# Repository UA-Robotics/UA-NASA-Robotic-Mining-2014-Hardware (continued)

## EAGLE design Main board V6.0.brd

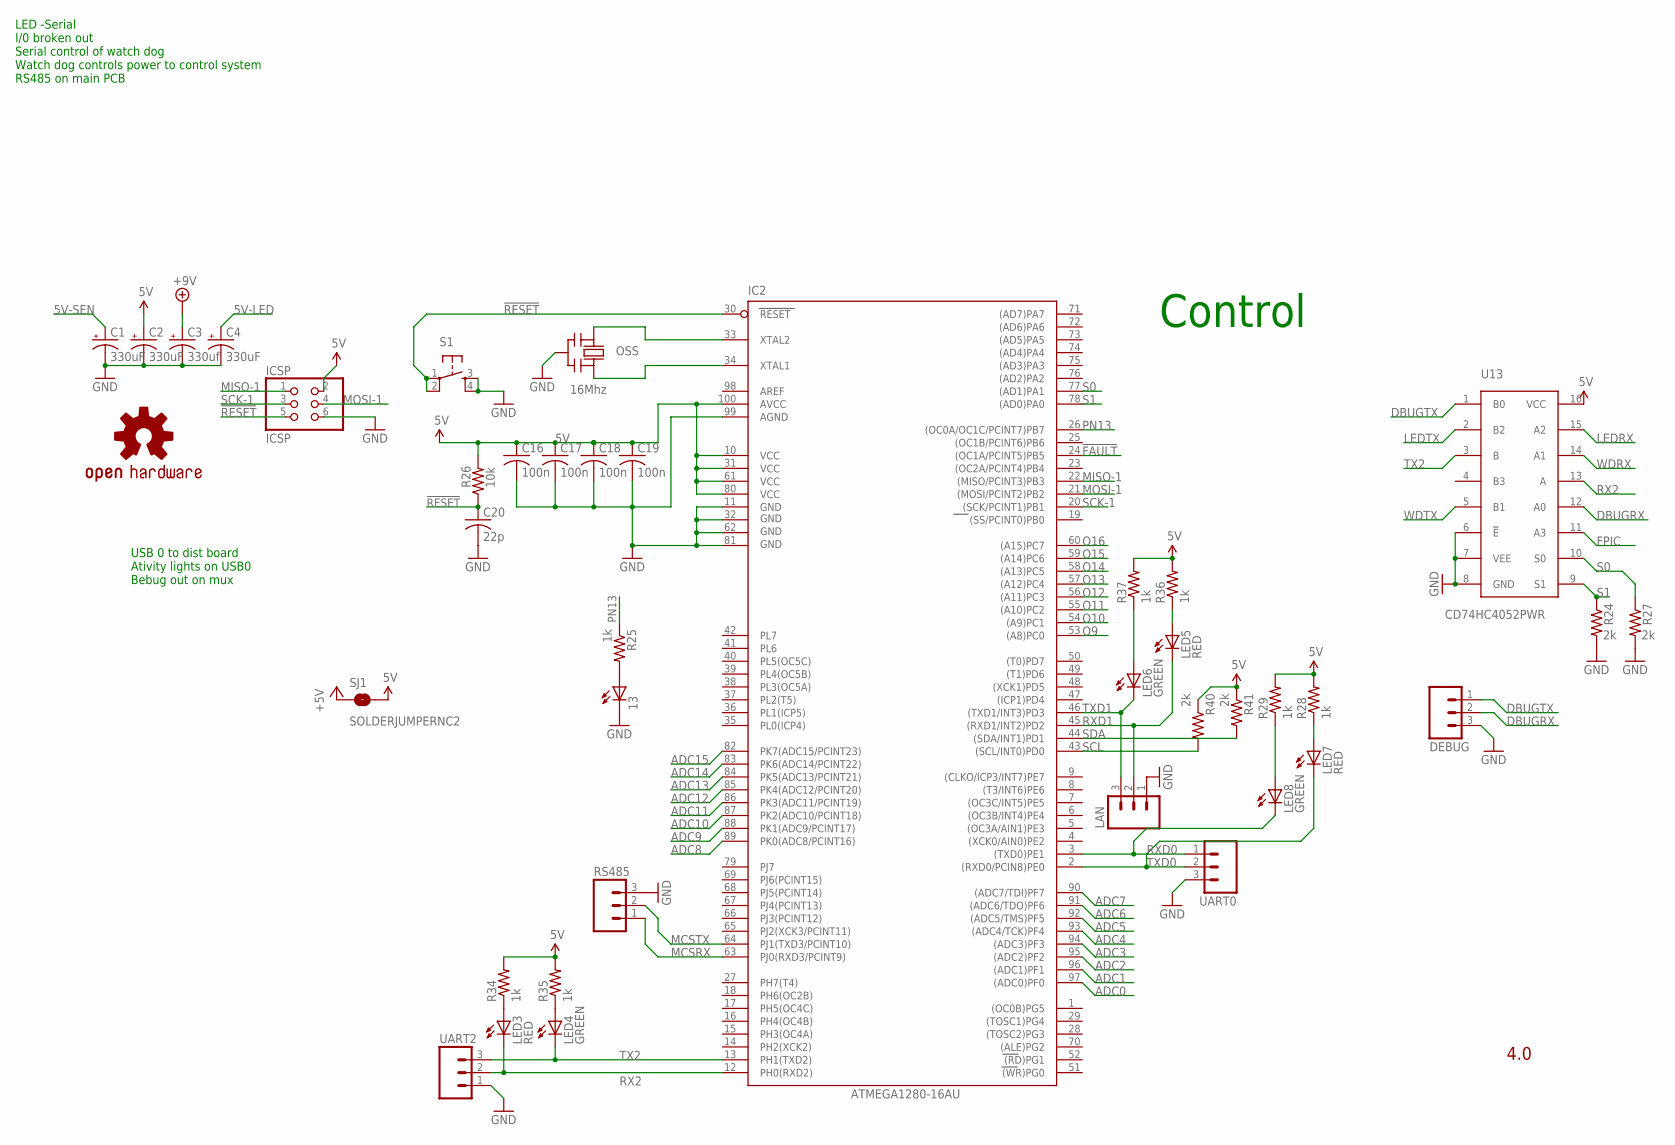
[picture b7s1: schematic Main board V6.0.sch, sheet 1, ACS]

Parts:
13: LEDCHIP-LED0805; CHIP-LED0805
C1, C2, C4: 330uF; 140CLH-0810
C3: 330uf; 140CLH-0810
C16, C17, C18, C19: 100n; C0805
C20: 22p; C0805
DEBUG: M03LOCK; 1X03_LOCK
IC2: ATMEGA1280-16AU; TQFP100
ICSP: ICSP; 2X03
LAN: M03LOCK; 1X03_LOCK
LED3, LED5, LED7: RED; CHIP-LED0805
LED4, LED6, LED8: GREEN; CHIP-LED0805
OSS: 16Mhz; AWCSR
R24, R27, R40, R41: 2k; R0805
R25, R28, R29, R34, R35, R36, R37: 1k; R0805
R26: 10k; R0805
RS485: M03LOCK; 1X03_LOCK
S1: TAC_SWITCHSMD; TACTILE_SWITCH_SMD
SJ1: SOLDERJUMPERNC2; SJ_2S-NOTRACE
U13: CD74HC4052PWR; TSSOP-16
U$3: OSHW-LOGOL; OSHW-LOGO-L
UART0: M03LOCK; 1X03_LOCK
UART2: M03POLAR; MOLEX-1X3

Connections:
5V: C2.+, C16.1, C17.1, C18.1, C19.1, IC2.10 (VCC), IC2.31 (VCC1), IC2.61 (VCC2), IC2.80 (VCC3), IC2.100 (AVCC), ICSP.2, R26.2, R28.2, R29.2, R34.2, R35.2, R36.2, R37.2, R40.1, R41.1, SJ1.2, U13.16 (VCC); also elsewhere on the board
5V-LED: C4.+; also elsewhere on the board
5V-SEN: C1.+; also elsewhere on the board
!FAULT: IC2.24 ((OC1A/PCINT5)PB5)
!RESET: C20.1, IC2.30 (RESET), ICSP.5, R26.1, S1.1, S1.2
+5V: SJ1.1; also elsewhere on the board
+9V: C3.+; also elsewhere on the board
ADC0: IC2.97 ((ADC0)PF0); also elsewhere on the board
ADC1: IC2.96 ((ADC1)PF1); also elsewhere on the board
ADC2: IC2.95 ((ADC2)PF2); also elsewhere on the board
ADC3: IC2.94 ((ADC3)PF3); also elsewhere on the board
ADC4: IC2.93 ((ADC4/TCK)PF4); also elsewhere on the board
ADC5: IC2.92 ((ADC5/TMS)PF5); also elsewhere on the board
ADC6: IC2.91 ((ADC6/TDO)PF6); also elsewhere on the board
ADC7: IC2.90 ((ADC7/TDI)PF7); also elsewhere on the board
ADC8: IC2.89 (PK0(ADC8/PCINT16)); also elsewhere on the board
ADC9: IC2.88 (PK1(ADC9/PCINT17)); also elsewhere on the board
ADC10: IC2.87 (PK2(ADC10/PCINT18)); also elsewhere on the board
ADC11: IC2.86 (PK3(ADC11/PCINT19)); also elsewhere on the board
ADC12: IC2.85 (PK4(ADC12/PCINT20)); also elsewhere on the board
ADC13: IC2.84 (PK5(ADC13/PCINT21)); also elsewhere on the board
ADC14: IC2.83 (PK6(ADC14/PCINT22)); also elsewhere on the board
ADC15: IC2.82 (PK7(ADC15/PCINT23)); also elsewhere on the board
DBUGRX: DEBUG.2, U13.12 (A0)
DBUGTX: DEBUG.1, U13.1 (B0)
FPIC: U13.11 (A3); also elsewhere on the board
GND: 13.C, C1.-, C2.-, C3.-, C4.-, C16.2, C17.2, C18.2, C19.2, C20.2, DEBUG.3, IC2.11 (GND), IC2.32 (GND1), IC2.62 (GND2), IC2.81 (GND3), IC2.99 (AGND), ICSP.6, LAN.1, OSS.2 (GND), R24.2, R27.2, RS485.3, S1.3, S1.4, U13.6 (!E), U13.7 (VEE), U13.8 (GND), UART0.3, UART2.1; also elsewhere on the board
LEDRX: U13.15 (A2); also elsewhere on the board
LEDTX: U13.2 (B2); also elsewhere on the board
MCSRX: IC2.63 (PJ0(RXD3/PCINT9)), RS485.1; also elsewhere on the board
MCSTX: IC2.64 (PJ1(TXD3/PCINT10)), RS485.2; also elsewhere on the board
MISO-1: IC2.22 ((MISO/PCINT3)PB3), ICSP.1
MOSI-1: IC2.21 ((MOSI/PCINT2)PB2), ICSP.4
unnamed: 13.A, R25.2
unnamed: IC2.34 (XTAL1), OSS.3 (OUT)
unnamed: IC2.33 (XTAL2), OSS.1 (IN)
unnamed: LED8.A, R29.1
unnamed: LED4.A, R35.1
unnamed: LED3.A, R34.1
unnamed: LED7.A, R28.1
unnamed: LED6.A, R37.1
unnamed: LED5.A, R36.1
O9: IC2.53 ((A8)PC0)
O10: IC2.54 ((A9)PC1)
O11: IC2.55 ((A10)PC2)
O12: IC2.56 ((A11)PC3)
O13: IC2.57 ((A12)PC4)
O14: IC2.58 ((A13)PC5)
O15: IC2.59 ((A14)PC6)
O16: IC2.60 ((A15)PC7)
PN13: IC2.26 ((OC0A/OC1C/PCINT7)PB7), R25.1; also elsewhere on the board
RX2: IC2.12 (PH0(RXD2)), LED3.C, U13.13 (A), UART2.2
RXD0: IC2.3 ((TXD0)PE1), LED8.C, UART0.1; also elsewhere on the board
RXD1: IC2.45 ((RXD1/INT2)PD2), LAN.2, LED5.C; also elsewhere on the board
S0: IC2.77 ((AD1)PA1), R27.1, U13.10 (S0)
S1: IC2.78 ((AD0)PA0), R24.1, U13.9 (S1)
SCK-1: IC2.20 ((SCK/PCINT1)PB1), ICSP.3
SCL: IC2.43 ((SCL/INT0)PD0), R40.2; also elsewhere on the board
SDA: IC2.44 ((SDA/INT1)PD1), R41.2; also elsewhere on the board
TX2: IC2.13 (PH1(TXD2)), LED4.C, U13.3 (B), UART2.3
TXD0: IC2.2 ((RXD0/PCIN8)PE0), LED7.C, UART0.2; also elsewhere on the board
TXD1: IC2.46 ((TXD1/INT3)PD3), LAN.3, LED6.C; also elsewhere on the board
WDRX: U13.14 (A1); also elsewhere on the board
WDTX: U13.5 (B1); also elsewhere on the board

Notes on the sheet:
4.0
Control
LED -Serial I/0 broken out Serial control of watch dog Watch dog controls power to control system RS485 on main PCB
USB 0 to dist board Ativity lights on USB0 Bebug out on mux

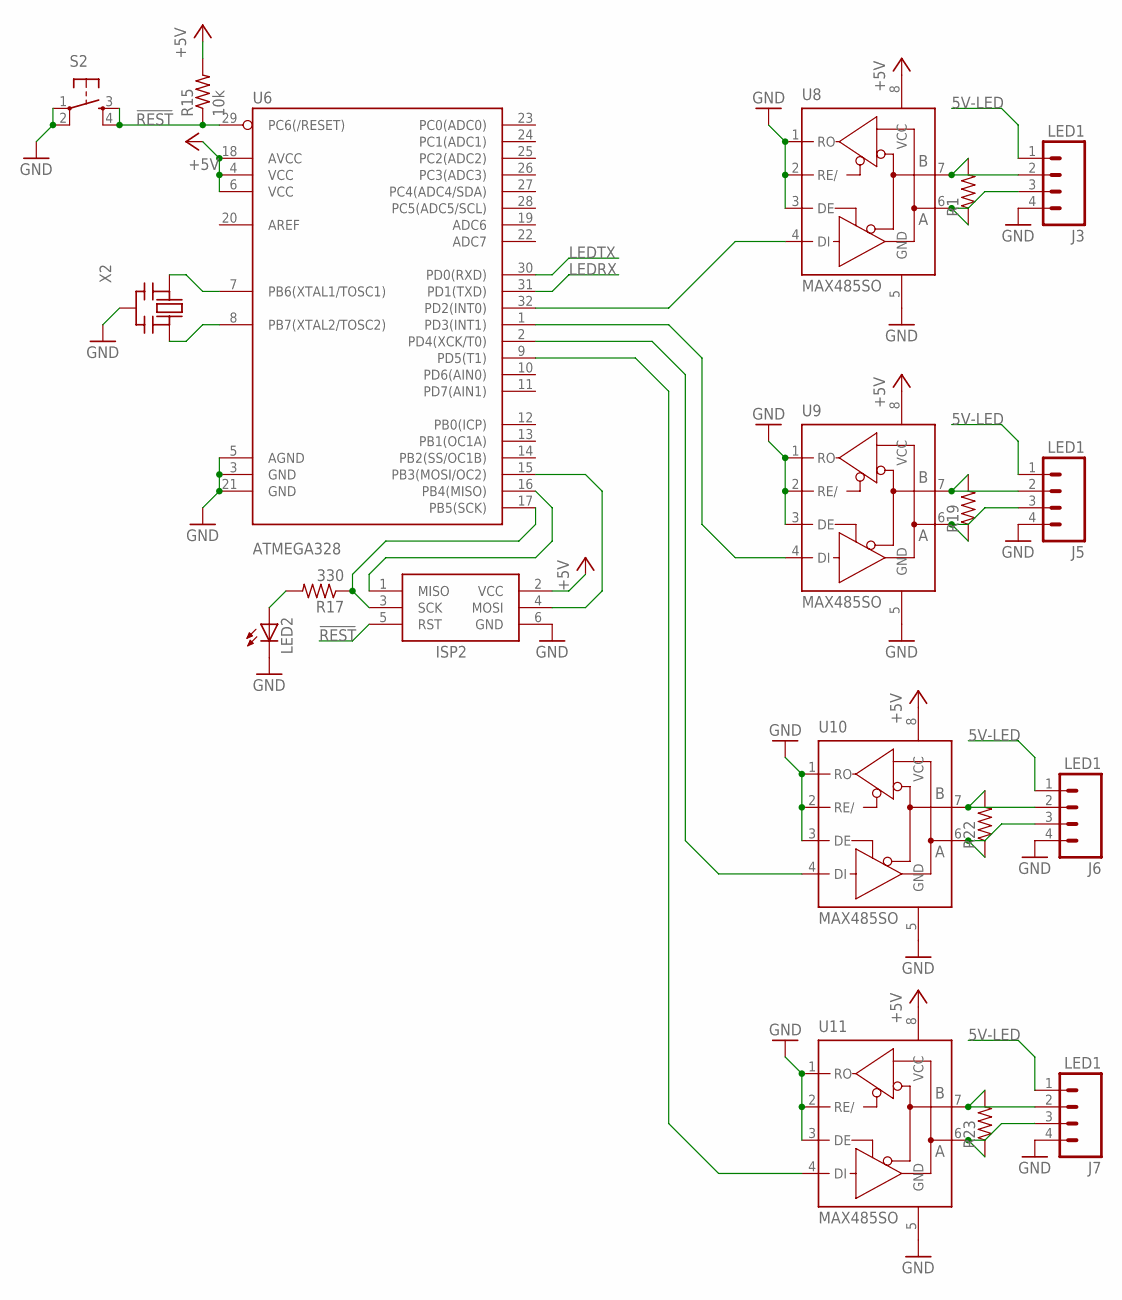
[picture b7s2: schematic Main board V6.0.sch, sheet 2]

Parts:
ISP2: AVRISP-6; AVRISP
J3, J5, J6, J7: LED1; M4
LED2: LEDCHIPLED_0805; CHIPLED_0805
R1, R19, R22, R23: RESISTOR0805-RES; 0805
R15: 10k; R0805
R17: 330; R0805
S2: TAC_SWITCHPTH; TACTILE-PTH
U6: ATMEGA328; TQFP32-08
U8, U9, U10, U11: MAX485SO; SO08
X2: CERMOSCILL-AWCSR; AWCSR

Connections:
5V-LED: J3.1, J5.1, J6.1, J7.1; also elsewhere on the board
!REST: ISP2.5 (RST), R15.1, S2.3, S2.4, U6.29 (PC6(/RESET))
+5V: ISP2.2 (VCC), R15.2, U6.4 (VCC), U6.6 (VCC), U6.18 (AVCC), U8.8 (VCC), U9.8 (VCC), U10.8 (VCC), U11.8 (VCC); also elsewhere on the board
DFDFD: ISP2.1 (MISO), U6.16 (PB4(MISO))
GND: ISP2.6 (GND), J3.4, J5.4, J6.4, J7.4, LED2.C, S2.1, S2.2, U6.3 (GND), U6.5 (AGND), U6.21 (GND), U8.1 (RO), U8.2 (RE/), U8.3 (DE), U8.5 (GND), U9.1 (RO), U9.2 (RE/), U9.3 (DE), U9.5 (GND), U10.1 (RO), U10.2 (RE/), U10.3 (DE), U10.5 (GND), U11.1 (RO), U11.2 (RE/), U11.3 (DE), U11.5 (GND), X2.2 (GND); also elsewhere on the board
LEDRX: U6.31 (PD1(TXD)); also elsewhere on the board
LEDTX: U6.30 (PD0(RXD)); also elsewhere on the board
unnamed: ISP2.3 (SCK), R17.1, U6.17 (PB5(SCK))
unnamed: ISP2.4 (MOSI), U6.15 (PB3(MOSI/OC2))
unnamed: LED2.A, R17.2
unnamed: U6.7 (PB6(XTAL1/TOSC1)), X2.1 (IN)
unnamed: U6.8 (PB7(XTAL2/TOSC2)), X2.3 (OUT)
unnamed: J3.2, R1.2, U8.7 (B)
unnamed: J3.3, R1.1, U8.6 (A)
unnamed: J5.2, R19.2, U9.7 (B)
unnamed: J5.3, R19.1, U9.6 (A)
unnamed: J6.2, R22.2, U10.7 (B)
unnamed: J6.3, R22.1, U10.6 (A)
unnamed: J7.2, R23.2, U11.7 (B)
unnamed: J7.3, R23.1, U11.6 (A)
unnamed: U6.32 (PD2(INT0)), U8.4 (DI)
unnamed: U6.1 (PD3(INT1)), U9.4 (DI)
unnamed: U6.2 (PD4(XCK/T0)), U10.4 (DI)
unnamed: U6.9 (PD5(T1)), U11.4 (DI)

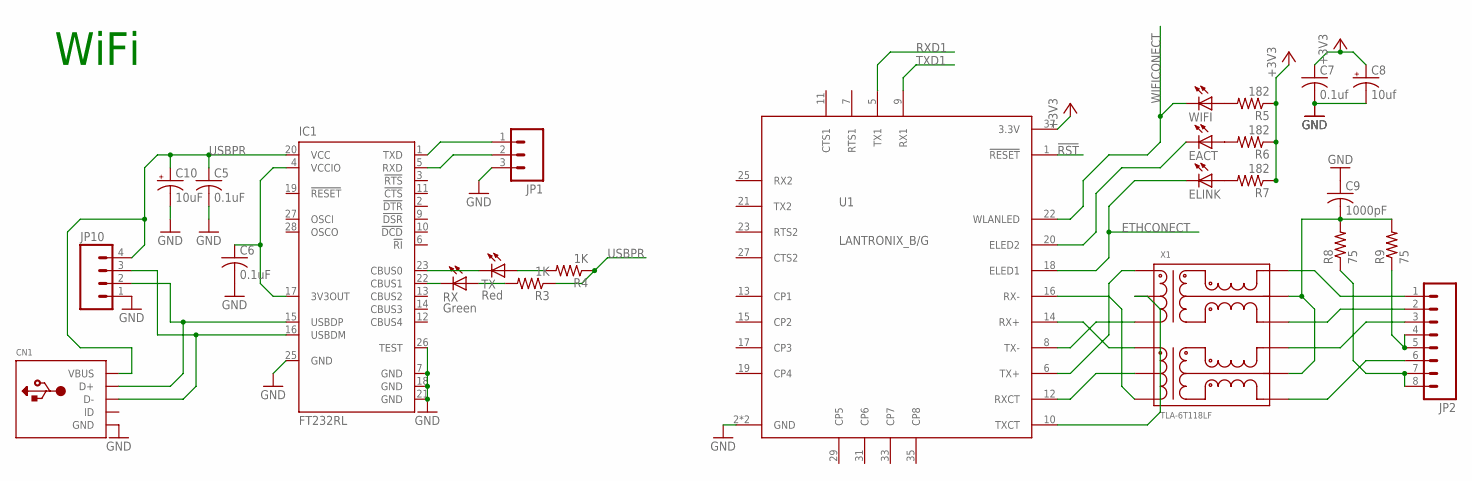
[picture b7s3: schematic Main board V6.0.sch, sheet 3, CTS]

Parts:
C5, C6: 0.1uF; C0805K
C7: 0.1uf; C0805K
C8: 10uf; EIA3528
C9: 1000pF; C1812
C10: 10uF; EIA3528-KIT
CN1: USBMINIB; USB-MINIB
EACT: LEDCHIP-LED0805; CHIP-LED0805
ELINK: LEDCHIP-LED0805; CHIP-LED0805
IC1: FT232RL; SSOP28
JP1: M03POLAR; MOLEX-1X3
JP2: M08LOCK; 1X08_LOCK
JP10: M04POLAR; MOLEX-1X4
R3, R4: 1K; R0805
R5, R6, R7: 182; R0805
R8, R9: 75; R0805
RX: Green; CHIP-LED0805
TX: Red; CHIP-LED0805
U1: LANTRONIX_B/G; LANA/BTH
WIFI: LEDCHIP-LED0805; CHIP-LED0805
X1: TLA-6T118LF; SO-16MOD

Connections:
!RST: U1.1 (!RESET)
+3V3: C7.1, C8.A (+), R5.1, R6.1, R7.1, U1.37 (3.3V); also elsewhere on the board
ETHCONECT: ELINK.C, U1.18 (ELED1)
GND: C5.2, C6.2, C7.2, C8.C (-), C9.1, C10.C (-), CN1.GND, IC1.7 (GND), IC1.18 (GND), IC1.21 (GND), IC1.25 (GND), IC1.26 (TEST), JP1.3, JP10.1, U1.2 (GND), U1.39 (GND); also elsewhere on the board
unnamed: IC1.23 (CBUS0), TX.C
unnamed: IC1.22 (CBUS1), RX.C
unnamed: R3.2, RX.A
unnamed: CN1.D+, IC1.15 (USBDP), JP10.2
unnamed: CN1.D-, IC1.16 (USBDM), JP10.3
unnamed: R4.2, TX.A
unnamed: IC1.1 (TXD), JP1.1
unnamed: C6.1, IC1.4 (VCCIO), IC1.17 (3V3OUT)
unnamed: U1.8 (TX-), X1.3
unnamed: U1.6 (TX+), X1.1
unnamed: U1.14 (RX+), X1.6
unnamed: U1.16 (RX-), X1.8
unnamed: U1.12 (RXCT), X1.7
unnamed: U1.10 (TXCT), X1.2
unnamed: JP2.7, JP2.8, R8.1
unnamed: JP2.1, X1.16
unnamed: JP2.2, X1.14
unnamed: JP2.3, X1.11
unnamed: JP2.6, X1.9
unnamed: C9.2, R8.2, R9.2, X1.10, X1.15
unnamed: ELINK.A, R7.2
unnamed: EACT.A, R6.2
unnamed: R5.2, WIFI.A
unnamed: EACT.C, U1.20 (ELED2)
unnamed: JP2.4, JP2.5, R9.1
unnamed: IC1.5 (RXD), JP1.2
RXD1: U1.5 (TX1); also elsewhere on the board
TXD1: U1.9 (RX1); also elsewhere on the board
USBPR: C5.1, C10.A (+), CN1.VBUS, IC1.20 (VCC), JP10.4, R3.1, R4.1
WIFICONECT: U1.22 (WLANLED), WIFI.C

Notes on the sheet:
WiFi

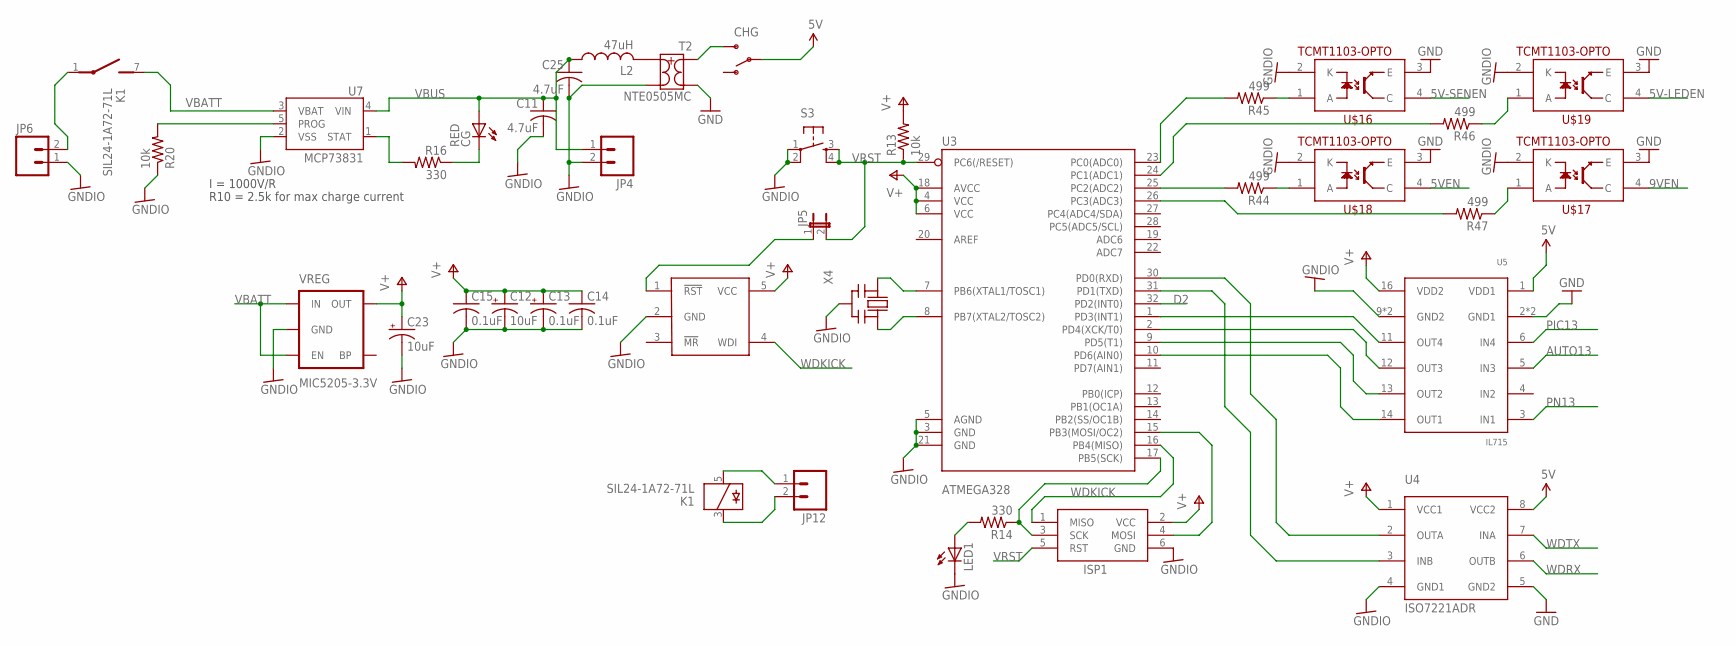
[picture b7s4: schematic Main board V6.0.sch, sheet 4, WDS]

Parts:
C11, C25: 4.7uF; C0603
C12, C23: 10uF; CT3528
C13: 0.1uF; CT3528
C14, C15: 0.1uF; C0805
CG: RED; SML0805
CHG: SWITCH-SPSTPTH; SWITCH-SPDT
ISP1: AVRISP-6; AVRISP
JP4: M021X02_NO_SILK; 1X02_NO_SILK
JP5: JUMPER-2PTH_LOCK; 1X02_LOCK
JP6: M02-JST-2MM-SMT; JST-2-SMD
JP12: M02POLAR_LOCK; MOLEX-1X2_LOCK
K1: SIL24-1A72-71L; REED
L2: 47uH; L2012C
LED1: LEDCHIPLED_0805; CHIPLED_0805
R13, R20: 10k; R0805
R14, R16: 330; R0805
R44, R45, R46, R47: 499; R0805
S3: TAC_SWITCHPTH; TACTILE-PTH
T2: NTE0505MC; SO-8FT
U3: ATMEGA328; TQFP32-08
U4: ISO7221ADR; SOIC-8
U5: IL715; S016
U7: MCP73831; SOT23-5
U20: MAX823; SOT23-5L
U$16, U$17, U$18, U$19: TCMT1103-OPTO; SSOP-4
VREG: MIC5205-3.3V; SOT23-5
X4: CERMOSCILL-CSTCRG; CSTCR-G

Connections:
5V: CHG.2, U4.8 (VCC2), U5.1 (VDD1); also elsewhere on the board
5V-LEDEN: U$19.4 (C); also elsewhere on the board
5V-SENEN: U$16.4 (C); also elsewhere on the board
5VEN: U$18.4 (C); also elsewhere on the board
9VEN: U$17.4 (C); also elsewhere on the board
AUTO13: U5.5 (IN3); also elsewhere on the board
D2: U3.32 (PD2(INT0))
GND: T2.1 (2), U4.5 (GND2), U5.2 (GND1), U5.8 (GND1), U$16.3 (E), U$17.3 (E), U$18.3 (E), U$19.3 (E); also elsewhere on the board
GNDIO: C11.2, C12.-, C13.-, C14.2, C15.2, C23.-, C25.2, ISP1.6 (GND), JP4.2, JP6.1, LED1.C, R20.1, S3.1, S3.2, T2.7 (3), U3.3 (GND), U3.5 (AGND), U3.21 (GND), U4.4 (GND1), U5.9 (GND2), U5.15 (GND2), U7.2 (VSS), U20.2 (GND), U$16.2 (K), U$17.2 (K), U$18.2 (K), U$19.2 (K), VREG.2 (GND), X4.2 (GND)
unnamed: U3.31 (PD1(TXD)), U4.3 (INB)
unnamed: JP5.1, U20.1 (!RST)
unnamed: ISP1.3 (SCK), R14.1, U3.17 (PB5(SCK))
unnamed: U3.30 (PD0(RXD)), U4.2 (OUTA)
unnamed: ISP1.4 (MOSI), U3.15 (PB3(MOSI/OC2))
unnamed: R45.2, U3.23 (PC0(ADC0))
unnamed: L2.2, T2.8 (4)
unnamed: LED1.A, R14.2
unnamed: CG.C, R16.1
unnamed: JP12.1, K1.5
unnamed: JP6.2, K1.1
unnamed: U3.7 (PB6(XTAL1/TOSC1)), X4.1 (IN)
unnamed: U3.8 (PB7(XTAL2/TOSC2)), X4.3 (OUT)
unnamed: U3.2 (PD4(XCK/T0)), U5.12 (OUT3)
unnamed: U3.9 (PD5(T1)), U5.13 (OUT2)
unnamed: U3.10 (PD6(AIN0)), U5.14 (OUT1)
unnamed: CHG.3 (S), T2.3 (1)
unnamed: U3.1 (PD3(INT1)), U5.11 (OUT4)
unnamed: R45.1, U$16.1 (A)
unnamed: R46.2, U3.24 (PC1(ADC1))
unnamed: R46.1, U$19.1 (A)
unnamed: R44.2, U3.25 (PC2(ADC2))
unnamed: R44.1, U$18.1 (A)
unnamed: R47.2, U3.26 (PC3(ADC3))
unnamed: R47.1, U$17.1 (A)
unnamed: JP12.2, K1.3
PIC13: U5.6 (IN4); also elsewhere on the board
PN13: U5.3 (IN1); also elsewhere on the board
PROG: R20.2, U7.5 (PROG)
STAT: R16.2, U7.1 (STAT)
V+: C12.+, C13.+, C14.1, C15.1, C23.+, ISP1.2 (VCC), R13.2, U3.4 (VCC), U3.6 (VCC), U3.18 (AVCC), U4.1 (VCC1), U5.16 (VDD2), U20.5 (VCC), VREG.5 (OUT)
VBATT: K1.7 (S), U7.3 (VBAT), VREG.1 (IN), VREG.3 (EN)
VBUS: C11.1, C25.1, CG.A, JP4.1, L2.1, U7.4 (VIN)
VRST: ISP1.5 (RST), JP5.2, R13.1, S3.3, S3.4, U3.29 (PC6(/RESET))
WDKICK: ISP1.1 (MISO), U3.16 (PB4(MISO)), U20.4 (WDI)
WDRX: U4.6 (OUTB); also elsewhere on the board
WDTX: U4.7 (INA); also elsewhere on the board

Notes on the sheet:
I = 1000V/R
R10 = 2.5k for max charge current

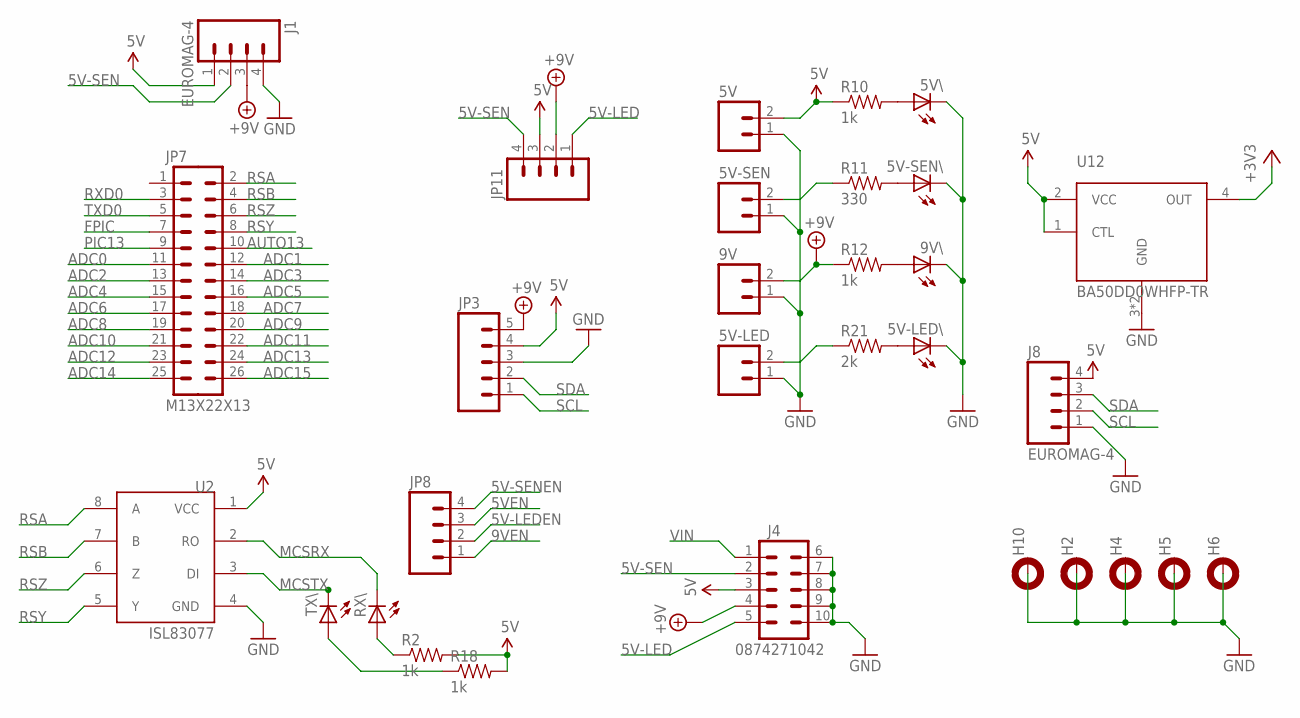
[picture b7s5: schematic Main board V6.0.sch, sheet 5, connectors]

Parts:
5V, 5V-LED, 5V-SEN, 9V: EUROMAG-290DEG; M2
5V-LED\, 5V-SEN\, 5V\, 9V\: LEDCHIP-LED0805; CHIP-LED0805
H2, H4, H5, H6, H10: MOUNT-PAD-ROUND2.8; 2,8-PAD
J1, J8: EUROMAG-4; M4
J4: 0874271042
JP3: M05LOCK_LONGPADS; 1X05_LOCK_LONGPADS
JP7: M13X22X13; 2X13
JP8: M04LOCK; 1X04_LOCK
JP11: M04POLAR; MOLEX-1X4
R2, R10, R12, R18: 1k; 0805
R11: 330; 0805
R21: 2k; 0805
RX\: LEDCHIP-LED0805; CHIP-LED0805
TX\: LEDCHIP-LED0805; CHIP-LED0805
U2: ISL83077; SO08
U12: BA50DD0WHFP-TR; HRP5

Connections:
5V: 5V.2, J1.1, J4.3, J8.4, JP3.4, JP11.3, R2.2, R10.1, R18.2, U2.1 (VCC), U12.1 (CTL), U12.2 (VCC); also elsewhere on the board
5V-LED: 5V-LED.2, J4.5, JP11.1, R21.1; also elsewhere on the board
5V-LEDEN: JP8.2; also elsewhere on the board
5V-SEN: 5V-SEN.2, J1.2, J4.2, JP11.4, R11.1; also elsewhere on the board
5V-SENEN: JP8.4; also elsewhere on the board
5VEN: JP8.3; also elsewhere on the board
9VEN: JP8.1; also elsewhere on the board
+3V3: U12.4 (OUT); also elsewhere on the board
+9V: 9V.2, J1.3, J4.4, JP3.5, JP11.2, R12.1; also elsewhere on the board
ADC0: JP7.11; also elsewhere on the board
ADC1: JP7.12; also elsewhere on the board
ADC2: JP7.13; also elsewhere on the board
ADC3: JP7.14; also elsewhere on the board
ADC4: JP7.15; also elsewhere on the board
ADC5: JP7.16; also elsewhere on the board
ADC6: JP7.17; also elsewhere on the board
ADC7: JP7.18; also elsewhere on the board
ADC8: JP7.19; also elsewhere on the board
ADC9: JP7.20; also elsewhere on the board
ADC10: JP7.21; also elsewhere on the board
ADC11: JP7.22; also elsewhere on the board
ADC12: JP7.23; also elsewhere on the board
ADC13: JP7.24; also elsewhere on the board
ADC14: JP7.25; also elsewhere on the board
ADC15: JP7.26; also elsewhere on the board
AUTO13: JP7.10; also elsewhere on the board
FPIC: JP7.7; also elsewhere on the board
GND: 5V.1, 5V-LED.1, 5V-LED\.C, 5V-SEN.1, 5V-SEN\.C, 5V\.C, 9V.1, 9V\.C, H2.B2,8, H4.B2,8, H5.B2,8, H6.B2,8, H10.B2,8, J1.4, J4.6, J4.7, J4.8, J4.9, J4.10, J8.1, JP3.3, U2.4 (GND), U12.3 (GND), U12.G (GND); also elsewhere on the board
MCSRX: RX\.C, U2.2 (RO); also elsewhere on the board
MCSTX: TX\.C, U2.3 (DI); also elsewhere on the board
unnamed: 5V\.A, R10.2
unnamed: R2.1, RX\.A
unnamed: R18.1, TX\.A
unnamed: 5V-SEN\.A, R11.2
unnamed: 9V\.A, R12.2
unnamed: 5V-LED\.A, R21.2
PIC13: JP7.9; also elsewhere on the board
RSA: JP7.2, U2.8 (A)
RSB: JP7.4, U2.7 (B)
RSY: JP7.8, U2.5 (Y)
RSZ: JP7.6, U2.6 (Z)
RXD0: JP7.3; also elsewhere on the board
SCL: J8.2, JP3.1; also elsewhere on the board
SDA: J8.3, JP3.2; also elsewhere on the board
TXD0: JP7.5; also elsewhere on the board
VIN: J4.1

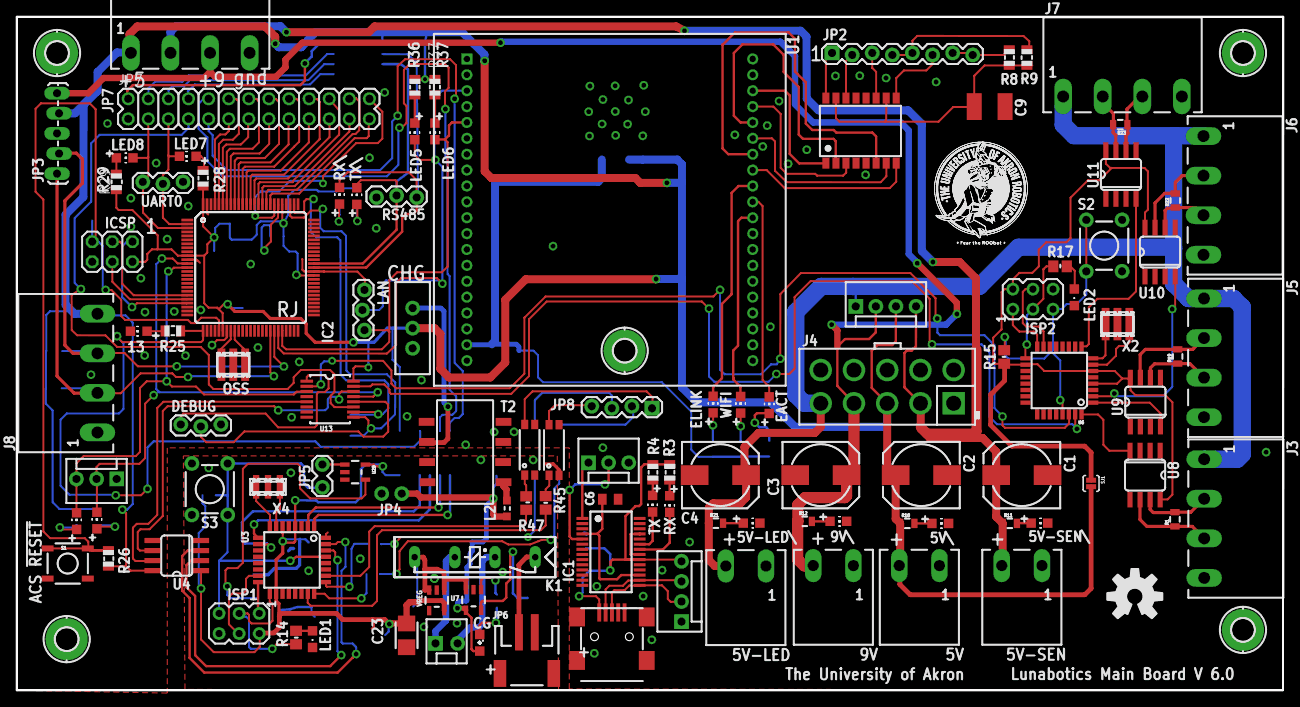
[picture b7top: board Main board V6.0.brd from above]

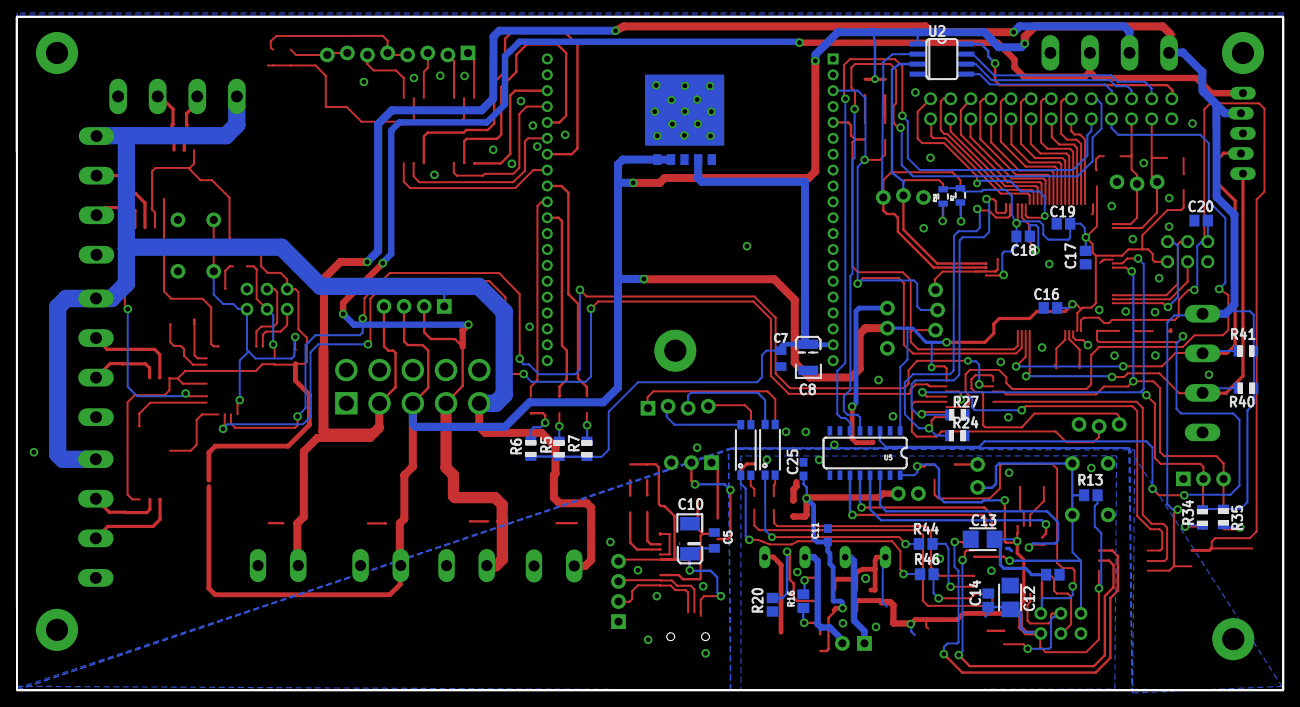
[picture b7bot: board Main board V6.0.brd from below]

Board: 2 copper layers, 160.0 x 85.1 mm, 152 parts (36 on the bottom side), 154 nets.

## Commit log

2015-08-14 Initial commit of the schematics for the 2014 year robot.
